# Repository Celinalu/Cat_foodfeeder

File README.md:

# Cat Feeder

## About
This cat feeder, as the name implies, is a food dispenser for my cat. It is an automatic feeder that will dispense food two times a day. It runs off an ESP32S3 and is paired with an RTC that controls the feeding time. The PCB is also connected to pins that will attach itself to a servo motor to complete the action of turning the door to dispense food. The power source of this feeder is from the USBC port connected to the PCB, and the USBC will get electricity from outside. 

## Parts explained 
PCB: I used Kicad to create the schematic and PCB. I took a look online to see what the main components were that other people used. And I found that it consisted of an MCU, a motor, a clock, and a display for the clock, so that is what I based my schematic on. I connected my ESP32S3 to a clock, and I added pins on my PCB to connect to a display as well as a servo motor. For the clock, I also added a small battery so it can run even if the feeder gets disconnected from power for a bit. There is also a button on the PCB meant for resetting the machine if that ever needs to be done. 

Case: For the case, I used Fusion 360. Before I made my case, I did a lot of research on what other people made. I found that there were two main disperser mechanisms that are commonly used: An arger and an open and closed mechanism (I hope that is understandable language). I ended up  using the open and closed door mechanism. Tweaking it slightly by making my door more like a turning door. Before I was worried about the weight of the kibble, but the whole dispenser isn't that big so there isn't a ton of kibble in there; the weight shouldn't be much of an issue. Other than that, everything else is pretty straightforward. There are two main spaces in the feeder. The top is for the PCB, while the bottom is kibble. 

Firmware: I tried to make it as simple as possible. Since the main purpose of the firmware is to program the times that the feeder will dispense food and let the servo know when it moves. I don't know if my firmware will even work yet, but it didnt give me any issues so I'll have to see if it works after I make the feeder.

## How to use 
The feeder has many lid-like tops, and the only screws in the whole machine are for the PCB to attach to the feeder. So the main thing that needs to be done is every couple of days to remove the top compartment and add kibble into it. I didn't use many screws because I thought it would be quite inconvenient to have to unscrew something every other day, since this whole machine is supposedly allowing you to become more lazy. Other than adding kibble, you don't really have to do anything!

## Why I made this
I decided to do this project since I thought that this would be a fun and useful project that I could actually use in my house, so it wouldn't become an object collecting dust. Compared to other machine-like projects, this one had relatively not amount of componnets, so it was still within my abilities to figure this project out.

# Zine

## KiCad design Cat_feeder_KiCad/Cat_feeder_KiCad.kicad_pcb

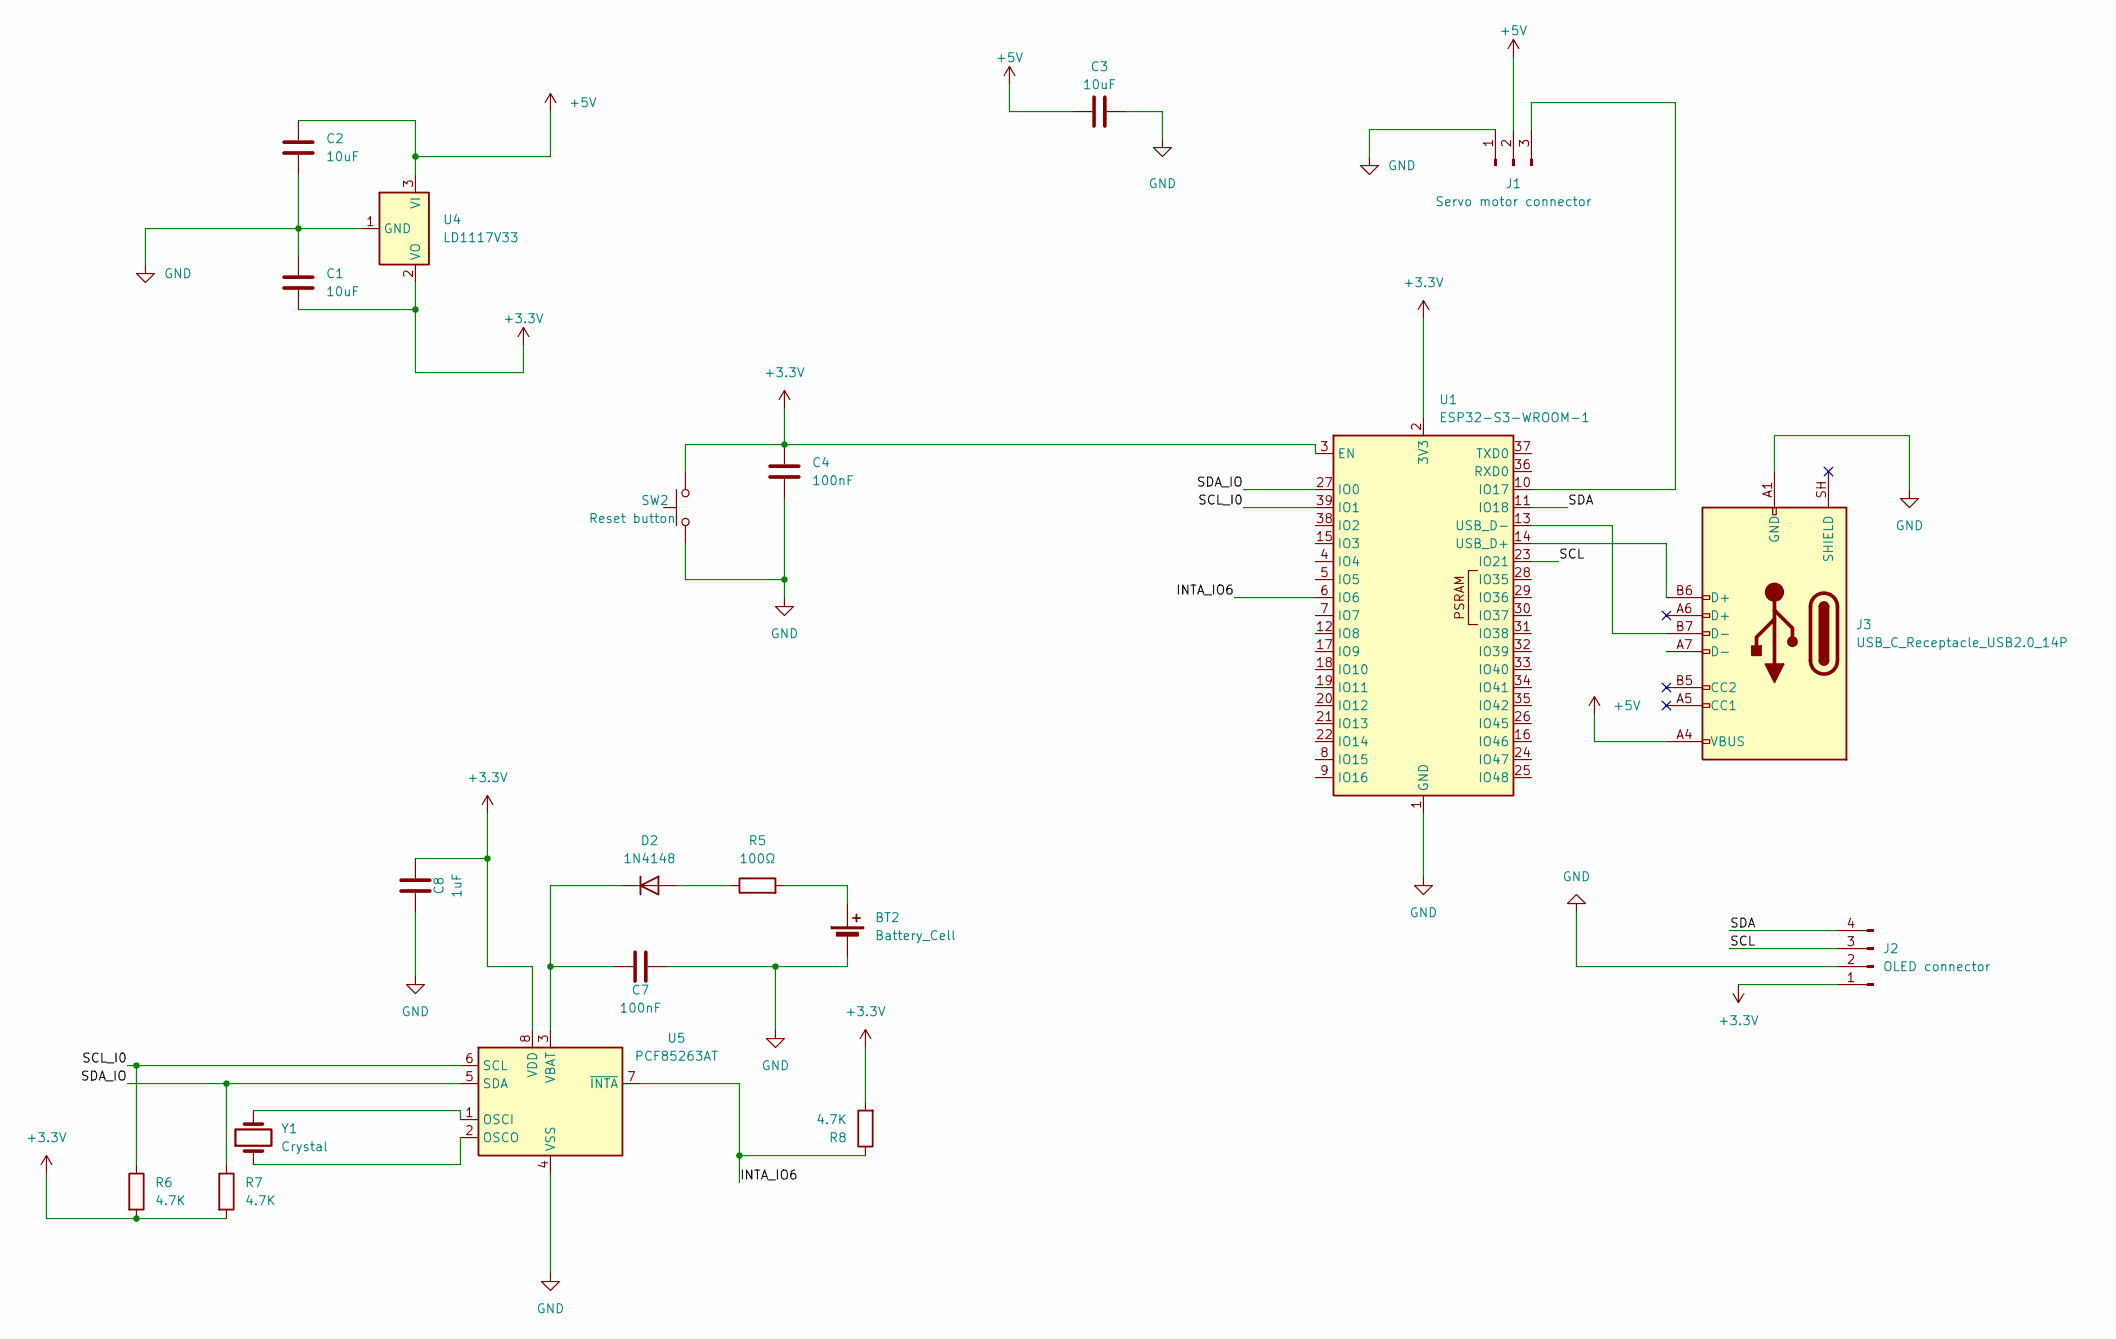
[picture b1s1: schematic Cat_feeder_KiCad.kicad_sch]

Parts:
BT2: Battery_Cell; BatteryHolder_Keystone_3034_1x20mm
C1, C2, C3: 10uF; C_0805_2012Metric
C4, C7: 100nF; C_0805_2012Metric
C8: 1uF; C_0805_2012Metric
D2: 1N4148; D_DO-35_SOD27_P7.62mm_Horizontal
J1: Servo motor connector; PinHeader_1x03_P2.54mm_Vertical
J2: OLED connector; PinHeader_1x04_P2.54mm_Vertical
J3: USB_C_Receptacle_USB2.0_14P; USB_C_Receptacle_HRO_TYPE-C-31-M-12
R5: 100Ω; R_0805_2012Metric
R6, R7, R8: 4.7K; R_0805_2012Metric
SW2: Reset button; SW_PUSH_6mm
U1: ESP32-S3-WROOM-1
U4: LD1117V33; TO-220-3_Vertical
U5: PCF85263AT; SOIC-8_3.9x4.9mm_P1.27mm
Y1: Crystal; Crystal_SMD_0603-2Pin_6.0x3.5mm

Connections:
+3.3V: C1.2, C4.1, C8.2, J2.1, R6.2, R7.2, R8.2, SW2.2, U1.2 (3V3), U1.3 (EN), U4.2 (VO), U5.8 (VDD)
+5V: C2.1, C3.2, J1.2, J3.A4 (VBUS), J3.A9 (VBUS), J3.B4 (VBUS), J3.B9 (VBUS), U4.3 (VI)
/INTA_IO6: R8.1, U1.6 (IO6), U5.7 (~INTA)
/SCL: J2.3, U1.23 (IO21)
/SCL_I0: R6.1, U1.39 (IO1), U5.6 (SCL)
/SDA: J2.4, U1.11 (IO18)
/SDA_IO: R7.1, U1.27 (IO0), U5.5 (SDA)
GND: BT2.2 (-), C1.1, C2.2, C3.1, C4.2, C7.2, C8.1, J1.1, J2.2, J3.A1 (GND), J3.A12 (GND), J3.B1 (GND), J3.B12 (GND), SW2.1, U1.1 (GND), U1.40 (GND), U1.41 (GND), U4.1 (GND), U5.4 (VSS)
unnamed: BT2.1 (+), R5.2
unnamed: D2.2 (A), R5.1
unnamed: C7.1, D2.1 (K), U5.3 (VBAT)
unnamed: J1.3, U1.10 (IO17)
unnamed: J3.B6 (D+), U1.14 (USB_D+)
unnamed: J3.B7 (D-), U1.13 (USB_D-)
unnamed: U5.1 (OSCI), Y1.2
unnamed: U5.2 (OSCO), Y1.1

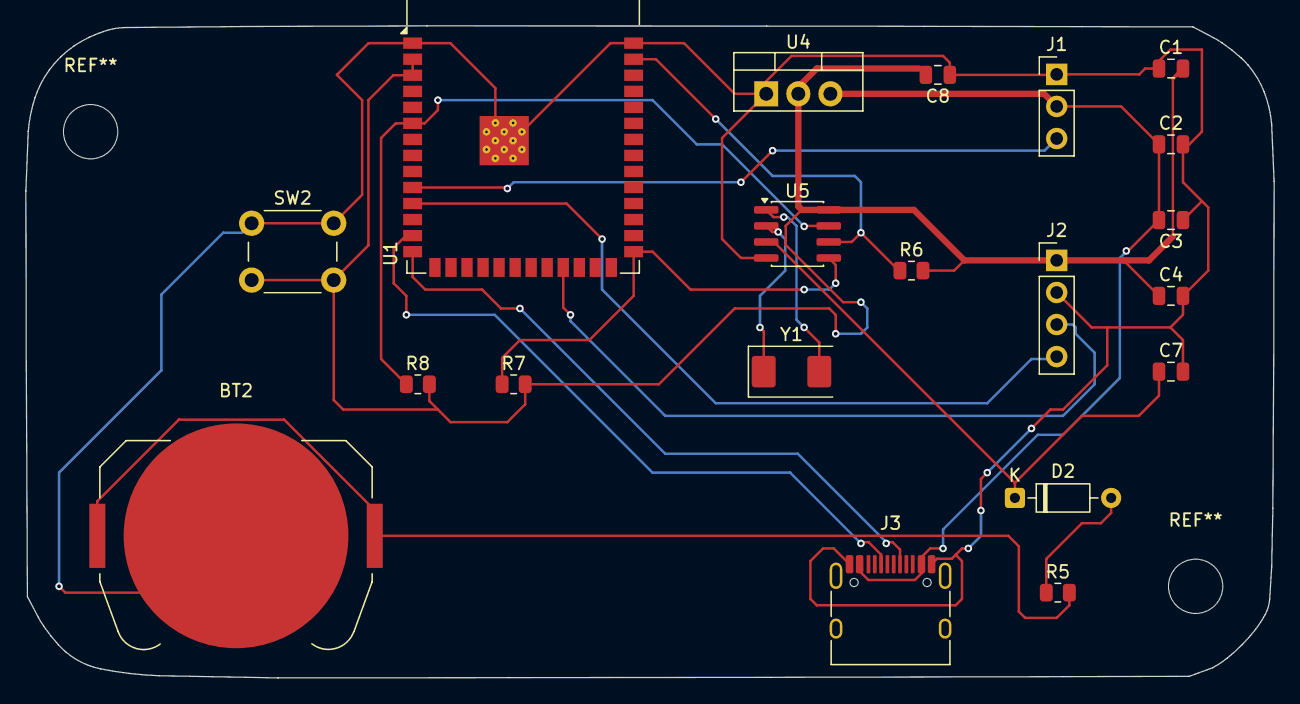
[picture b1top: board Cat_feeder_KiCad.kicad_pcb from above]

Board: 2 copper layers, 98.8 x 51.6 mm, 20 parts (0 on the bottom side), 16 nets.

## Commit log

2026-04-26 starting schematic trying to find parts
2026-04-27 doing schematic going okay ig...
2026-04-27 editing schematic
2026-04-28 polishing and editing schematic
2026-04-30 added a sub page onto my schematic
2026-04-30 saving some stuff I forgot to save before
2026-05-01 changing schematic bc I was dumb yesterday
2026-05-02 doing schematic
2026-05-02 adding footprints
2026-05-04 some schematic work + kicad crashed
2026-05-04 finished pcb
2026-05-04 done for the day
2026-05-06 added mounting holes
2026-06-01 updated cuz i forgot my power source
2026-06-07 deleted a button
2026-06-07 Update README with project details and instructions
    Added detailed project description, parts explanation, usage instructions, and motivation for creating the cat feeder.
2026-06-07 Add screenshot to README
    Added an image screenshot to the README.
